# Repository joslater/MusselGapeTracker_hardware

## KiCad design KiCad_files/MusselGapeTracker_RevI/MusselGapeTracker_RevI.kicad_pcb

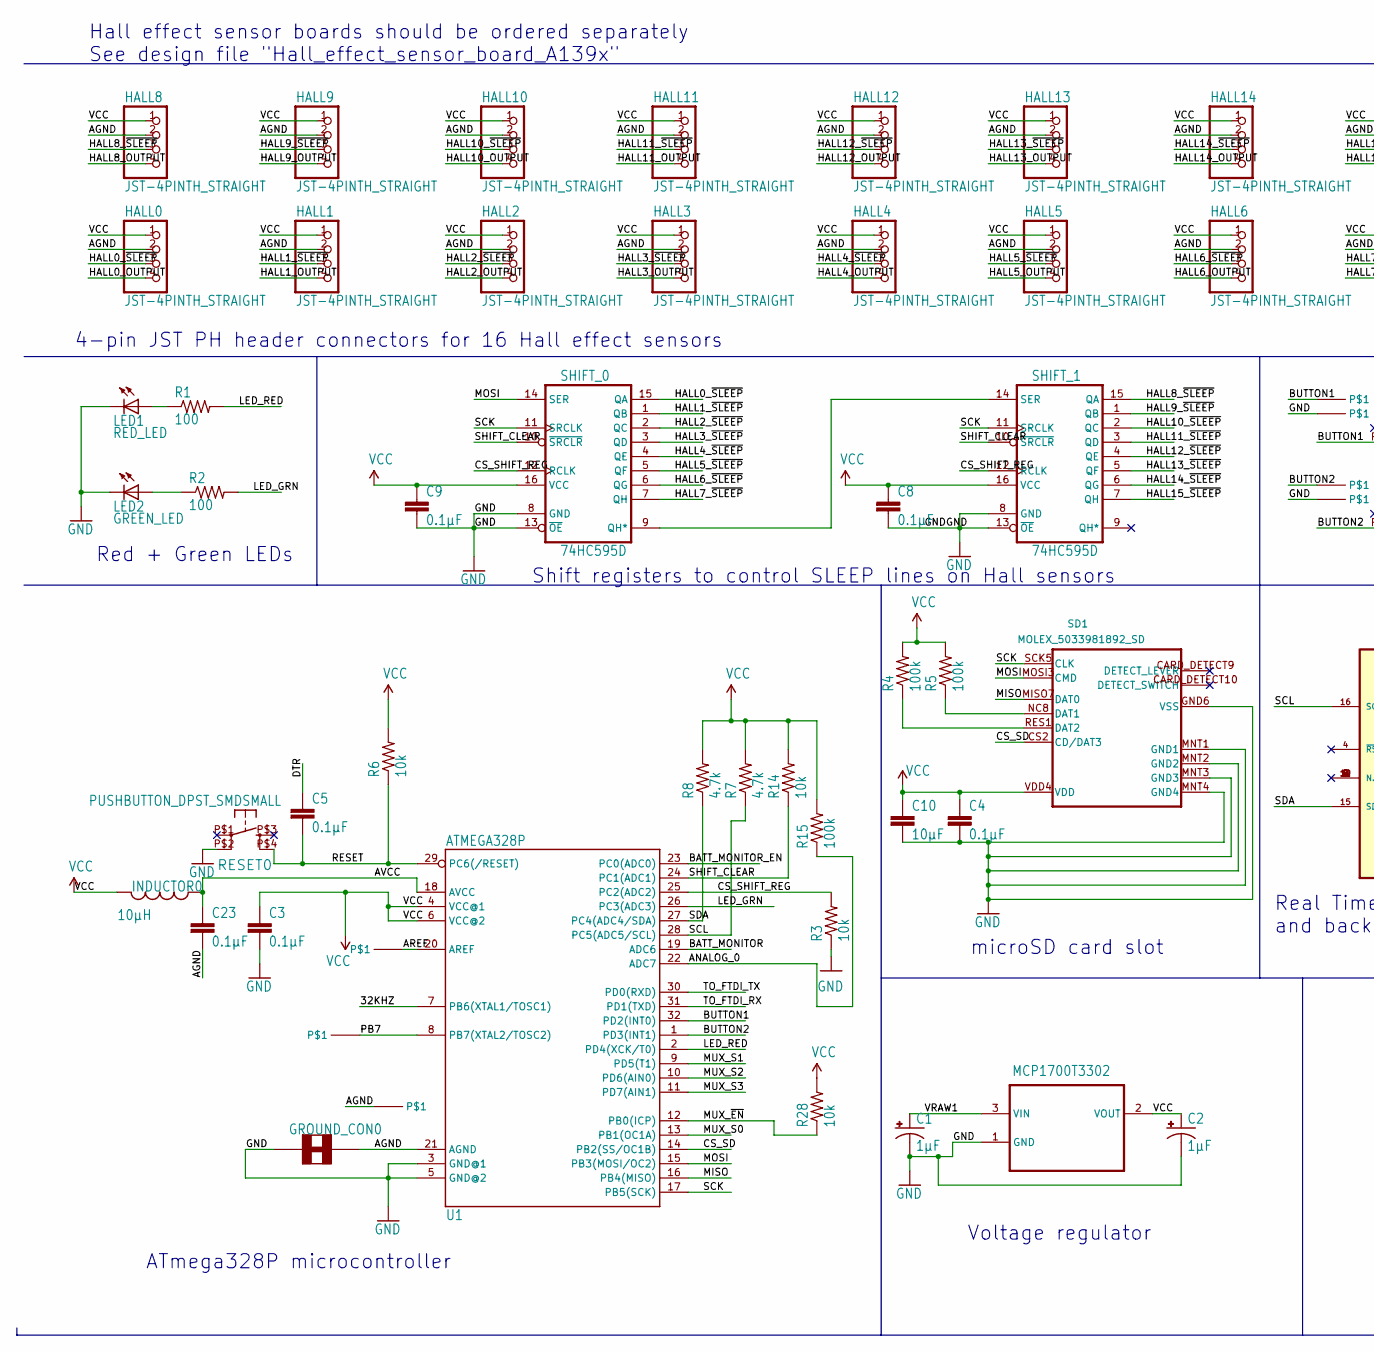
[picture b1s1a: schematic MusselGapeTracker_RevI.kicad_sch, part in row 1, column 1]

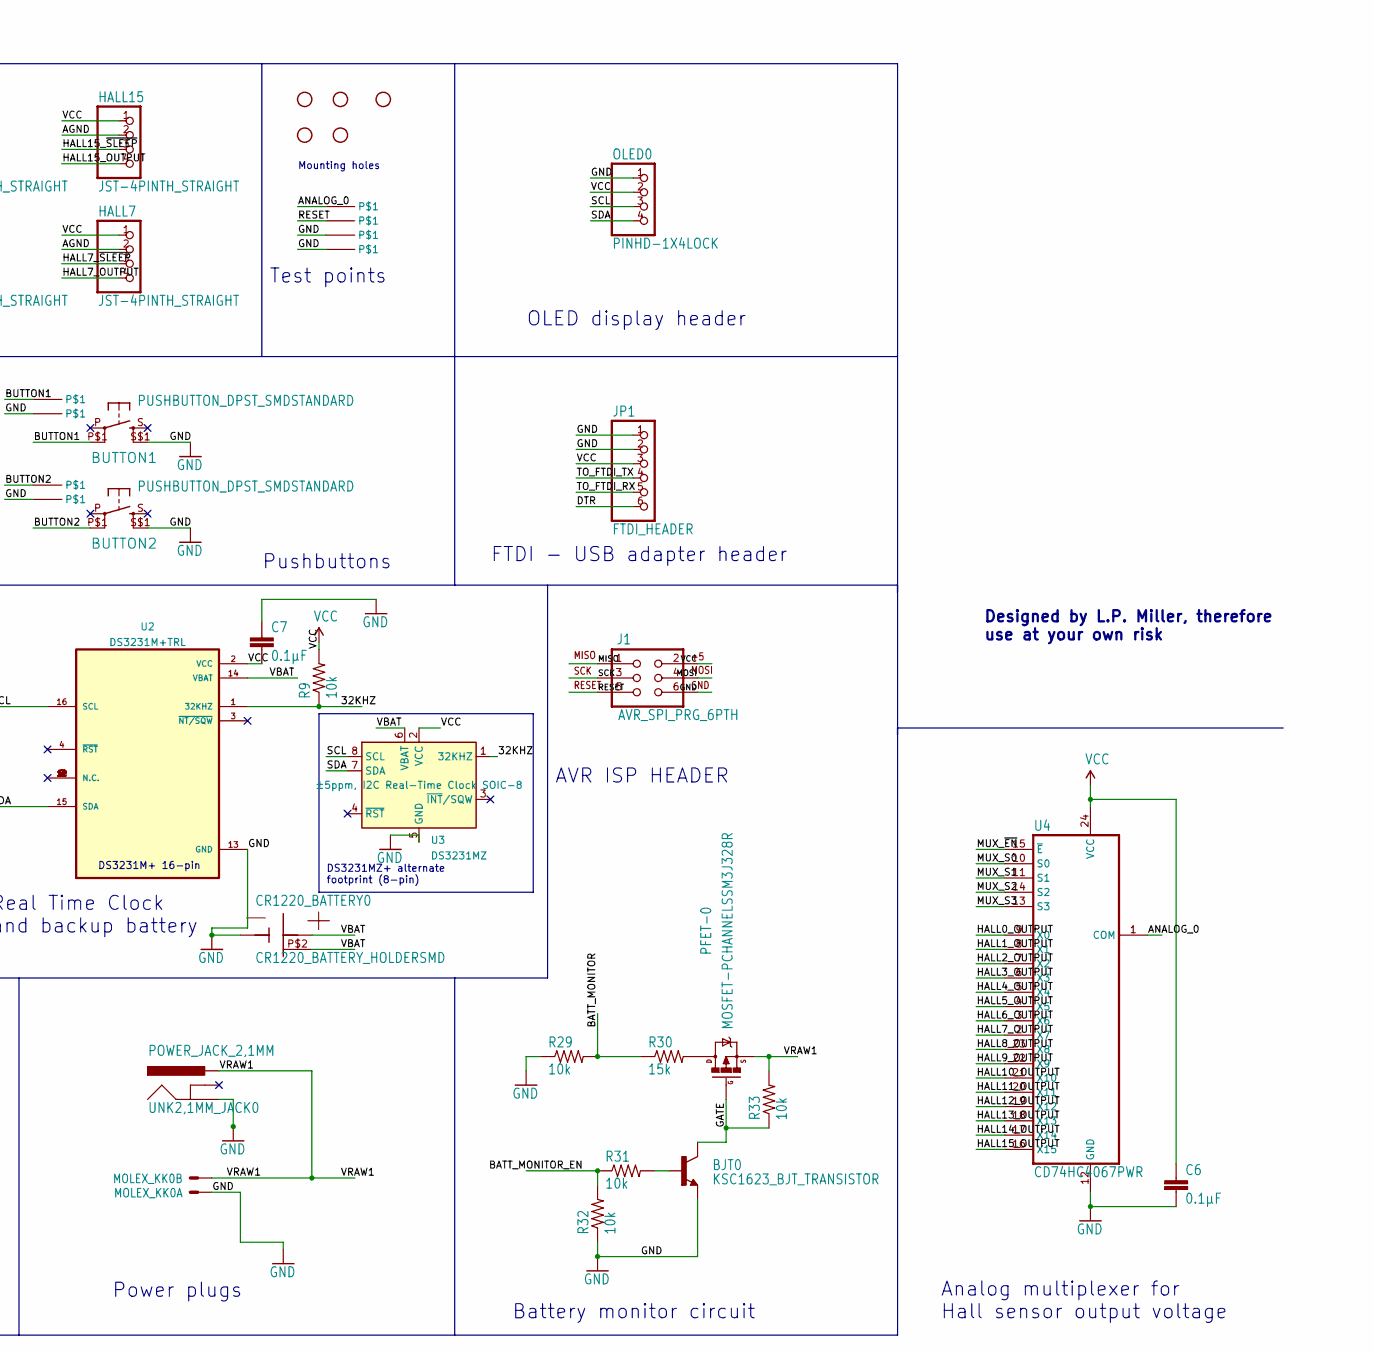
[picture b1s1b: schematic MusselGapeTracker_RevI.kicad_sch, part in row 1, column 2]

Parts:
BJT0: KSC1623_BJT_TRANSISTOR; SOT23
BUTTON1, BUTTON2: PUSHBUTTON_DPST_SMDSTANDARD; PUSHBUTTON_DPST_SMD
C1, C2: 1µF; PANASONIC_B
C3, C4, C5, C6, C7, C8, C9, C23: 0.1µF; R_0603_1608Metric_Pad0.98x0.95mm_HandSolder
C10: 10µF; R_0603_1608Metric_Pad0.98x0.95mm_HandSolder
CR1220_BATTERY0: CR1220_BATTERY_HOLDERSMD; CR1220_BATTERY_HOLDER_SMD
GND0: PINHD-1X1SMALL; 1X01_SMALL
GROUND_CON0: SOLDER_JUMPER_TRACESTANDARD; SJ_2S-TRACE
HALL0, HALL1, HALL2, HALL3, HALL4, HALL5, HALL6, HALL7, HALL8, HALL9, HALL10, HALL11, HALL12, HALL13, HALL14, HALL15: JST-4PINTH_STRAIGHT; JST-PH-4-THM
INDUCTOR0: 10µH; I_0805
J1: AVR_SPI_PRG_6PTH; 2X3
JP1: FTDI_HEADER; 1X06-RIGHT_ANGLE
LED1: RED_LED; CHIPLED_0805
LED2: GREEN_LED; CHIPLED_0805
MCP1700T3302: MCP1700T-3302E/TT; SOT95P237X112-3N
MOLEX_KK0: 22-23-2021
OLED0: PINHD-1X4LOCK; 1X04_LOCK
PB7: PINHD-1X1SMALL; 1X01_SMALL
PFET-0: MOSFET-PCHANNELSSM3J328R; SOT23-3
R1, R2: 100; R_0603_1608Metric_Pad0.98x0.95mm_HandSolder
R3, R6, R9, R14, R28, R29, R31, R32, R33: 10k; R_0603_1608Metric_Pad0.98x0.95mm_HandSolder
R4, R5, R15: 100k; R_0603_1608Metric_Pad0.98x0.95mm_HandSolder
R7, R8: 4.7k; R_0603_1608Metric_Pad0.98x0.95mm_HandSolder
R30: 15k; R_0603_1608Metric_Pad0.98x0.95mm_HandSolder
RESET0: PUSHBUTTON_DPST_SMDSMALL; PUSHBUTTON_SPST_PTS525_SERIES
SD1: MOLEX_5033981892_SD; CONN_503398-1892_MOL; PARTREV A
SHIFT_0, SHIFT_1: 74HC595D; SO16
STANDOFF1, STANDOFF2, STANDOFF3: STAND-OFF4-40; STAND-OFF
STANDOFF4_M2, STANDOFF5_M2: STAND-OFFM2; STAND-OFF_M2
U1: ATMEGA328P; TQFP32-08
U2: DS3231M+TRL; SOIC127P1032X265-16N
U3: DS3231MZ; SOIC-8_3.9x4.9mm_P1.27mm
U4: CD74HC4067PWR; TSSOP-24_4.4x7.8mm_P0.65mm
U$3, U$4, U$6, U$7, U$8, U$9, U$10, U$11, U$17: PINHD-1X1SMALL; 1X01_SMALL
UNK2,1MM_JACK0: POWER_JACK_2,1MM; POWER_JACK_DC_2,1MM

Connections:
/32KHZ: R9.1, U1.7 (PB6(XTAL1/TOSC1)), U2.1 (32KHZ), U3.1 (32KHZ)
/AGND: C23.2, GROUND_CON0.2, HALL0.2, HALL1.2, HALL2.2, HALL3.2, HALL4.2, HALL5.2, HALL6.2, HALL7.2, HALL8.2, HALL9.2, HALL10.2, HALL11.2, HALL12.2, HALL13.2, HALL14.2, HALL15.2, U1.21 (AGND), U$11.1 (P$1_1)
/ANALOG_0: R15.1, U1.22 (ADC7), U4.1 (COM), U$10.1 (P$1_1)
/AREF: U1.20 (AREF), U$17.1 (P$1_1)
/AVCC: C23.1, INDUCTOR0.P$1 (1), U1.18 (AVCC)
/BATT_MONITOR: R29.2, R30.1, U1.19 (ADC6)
/BATT_MONITOR_EN: R31.1, R32.2, U1.23 (PC0(ADC0))
/BUTTON1: BUTTON1.P$1 (P1), U1.32 (PD2(INT0)), U$6.1 (P$1_1)
/BUTTON2: BUTTON2.P$1 (P1), U1.1 (PD3(INT1)), U$8.1 (P$1_1)
/CS_SD: SD1.CS2 (CD/DAT3), U1.14 (PB2(SS/OC1B))
/CS_SHIFT_REG: R3.2, SHIFT_0.12 (RCLK), SHIFT_1.12 (RCLK), U1.25 (PC2(ADC2))
/DTR: C5.1, JP1.6
/GATE: BJT0.3 (C), PFET-0.1 (G), R33.1
/HALL0_OUTPUT: HALL0.4, U4.9 (X0)
/HALL0_~SLEEP: HALL0.3, SHIFT_0.15 (QA)
/HALL1_OUTPUT: HALL1.4, U4.8 (X1)
/HALL1_~SLEEP: HALL1.3, SHIFT_0.1 (QB)
/HALL2_OUTPUT: HALL2.4, U4.7 (X2)
/HALL2_~SLEEP: HALL2.3, SHIFT_0.2 (QC)
/HALL3_OUTPUT: HALL3.4, U4.6 (X3)
/HALL3_~SLEEP: HALL3.3, SHIFT_0.3 (QD)
/HALL4_OUTPUT: HALL4.4, U4.5 (X4)
/HALL4_~SLEEP: HALL4.3, SHIFT_0.4 (QE)
/HALL5_OUTPUT: HALL5.4, U4.4 (X5)
/HALL5_~SLEEP: HALL5.3, SHIFT_0.5 (QF)
/HALL6_OUTPUT: HALL6.4, U4.3 (X6)
/HALL6_~SLEEP: HALL6.3, SHIFT_0.6 (QG)
/HALL7_OUTPUT: HALL7.4, U4.2 (X7)
/HALL7_~SLEEP: HALL7.3, SHIFT_0.7 (QH)
/HALL8_OUTPUT: HALL8.4, U4.23 (X8)
/HALL8_~SLEEP: HALL8.3, SHIFT_1.15 (QA)
/HALL9_OUTPUT: HALL9.4, U4.22 (X9)
/HALL9_~SLEEP: HALL9.3, SHIFT_1.1 (QB)
/HALL10_OUTPUT: HALL10.4, U4.21 (X10)
/HALL10_~SLEEP: HALL10.3, SHIFT_1.2 (QC)
/HALL11_OUTPUT: HALL11.4, U4.20 (X11)
/HALL11_~SLEEP: HALL11.3, SHIFT_1.3 (QD)
/HALL12_OUTPUT: HALL12.4, U4.19 (X12)
/HALL12_~SLEEP: HALL12.3, SHIFT_1.4 (QE)
/HALL13_OUTPUT: HALL13.4, U4.18 (X13)
/HALL13_~SLEEP: HALL13.3, SHIFT_1.5 (QF)
/HALL14_OUTPUT: HALL14.4, U4.17 (X14)
/HALL14_~SLEEP: HALL14.3, SHIFT_1.6 (QG)
/HALL15_OUTPUT: HALL15.4, U4.16 (X15)
/HALL15_~SLEEP: HALL15.3, SHIFT_1.7 (QH)
/LED_GRN: R2.2, U1.26 (PC3(ADC3))
/LED_RED: R1.2, U1.2 (PD4(XCK/T0))
/MISO: J1.1, SD1.MISO7 (DAT0), U1.16 (PB4(MISO))
/MOSI: J1.4, SD1.MOSI3 (CMD), SHIFT_0.14 (SER), U1.15 (PB3(MOSI/OC2))
/MUX_S0: U1.13 (PB1(OC1A)), U4.10 (S0)
/MUX_S1: U1.9 (PD5(T1)), U4.11 (S1)
/MUX_S2: U1.10 (PD6(AIN0)), U4.14 (S2)
/MUX_S3: U1.11 (PD7(AIN1)), U4.13 (S3)
/MUX_~EN: R28.1, U1.12 (PB0(ICP)), U4.15 (~E)
/PB7: PB7.1 (P$1_1), U1.8 (PB7(XTAL2/TOSC2))
/RESET: C5.2, J1.5, R6.1, RESET0.P$4 (S1), U1.29 (PC6(/RESET)), U$3.1 (P$1_1)
/SCK: J1.3, SD1.SCK5 (CLK), SHIFT_0.11 (SRCLK), SHIFT_1.11 (SRCLK), U1.17 (PB5(SCK))
/SCL: OLED0.3, R7.1, U1.28 (PC5(ADC5/SCL)), U2.16 (SCL), U3.8 (SCL)
/SDA: OLED0.4, R8.1, U1.27 (PC4(ADC4/SDA)), U2.15 (SDA), U3.7 (SDA)
/SHIFT_CLEAR: R14.1, SHIFT_0.10 (~SRCLR), SHIFT_1.10 (~SRCLR), U1.24 (PC1(ADC1))
/TO_FTDI_RX: JP1.5, U1.31 (PD1(TXD))
/TO_FTDI_TX: JP1.4, U1.30 (PD0(RXD))
/VBAT: CR1220_BATTERY0.P$1 (VBAT), CR1220_BATTERY0.P$2, U2.14 (VBAT), U3.6 (VBAT)
/VRAW1: C1.+, MCP1700T3302.3 (VIN), MOLEX_KK0.2 (S), PFET-0.2 (S), R33.2, UNK2,1MM_JACK0.P$1 (PWR)
GND: BJT0.2 (E), BUTTON1.S$1 (S1), BUTTON2.S$1 (S1), C1.-, C2.-, C3.2, C4.2, C6.2, C7.1, C8.2, C9.2, C10.2, CR1220_BATTERY0.GND, GND0.1 (P$1_1), GROUND_CON0.1, J1.6, JP1.1, JP1.2, LED1.C, LED2.C, MCP1700T3302.1 (GND), MOLEX_KK0.1 (S), OLED0.1, R3.1, R29.1, R32.1, RESET0.P$2 (P1), SD1.GND6 (VSS), SD1.MNT1 (GND1), SD1.MNT2 (GND2), SD1.MNT3 (GND3), SD1.MNT4 (GND4), SHIFT_0.8 (GND), SHIFT_0.13 (~OE), SHIFT_1.8 (GND), SHIFT_1.13 (~OE), U1.3 (GND@1), U1.5 (GND@2), U2.13 (GND), U3.5 (GND), U4.12 (GND), U$4.1 (P$1_1), U$7.1 (P$1_1), U$9.1 (P$1_1), UNK2,1MM_JACK0.P$2 (GND)
unnamed: BJT0.1 (B), R31.2
unnamed: LED1.A, R1.1
unnamed: LED2.A, R2.1
unnamed: PFET-0.3 (D), R30.2
unnamed: R5.1, SD1.NC8 (DAT1)
unnamed: R4.1, SD1.RES1 (DAT2)
unnamed: SHIFT_0.9 (QH*), SHIFT_1.14 (SER)
VCC: C2.+, C3.1, C4.1, C6.1, C7.2, C8.1, C9.1, C10.1, HALL0.1, HALL1.1, HALL2.1, HALL3.1, HALL4.1, HALL5.1, HALL6.1, HALL7.1, HALL8.1, HALL9.1, HALL10.1, HALL11.1, HALL12.1, HALL13.1, HALL14.1, HALL15.1, INDUCTOR0.P$2 (2), J1.2, JP1.3, MCP1700T3302.2 (VOUT), OLED0.2, R4.2, R5.2, R6.2, R7.2, R8.2, R9.2, R14.2, R15.2, R28.2, SD1.VDD4 (VDD), SHIFT_0.16 (VCC), SHIFT_1.16 (VCC), U1.4 (VCC@1), U1.6 (VCC@2), U2.2 (VCC), U3.2 (VCC), U4.24 (VCC)

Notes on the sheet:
Voltage regulator
OLED display header
DS3231M+ 16-pin
microSD card slot
Real Time Clock and backup battery
Battery monitor circuit
4-pin JST PH header connectors for 16 Hall effect sensors
Hall effect sensor boards should be ordered separately See design file "Hall_effect_sensor_board_A139x"
Pushbuttons
Test points
Designed by L.P. Miller, therefore use at your own risk
ATmega328P microcontroller
FTDI - USB adapter header
Analog multiplexer for Hall sensor output voltage
Power plugs
Mounting holes
Shift registers to control SLEEP lines on Hall sensors
DS3231MZ+ alternate footprint (8-pin)
AVR ISP HEADER
Red + Green LEDs

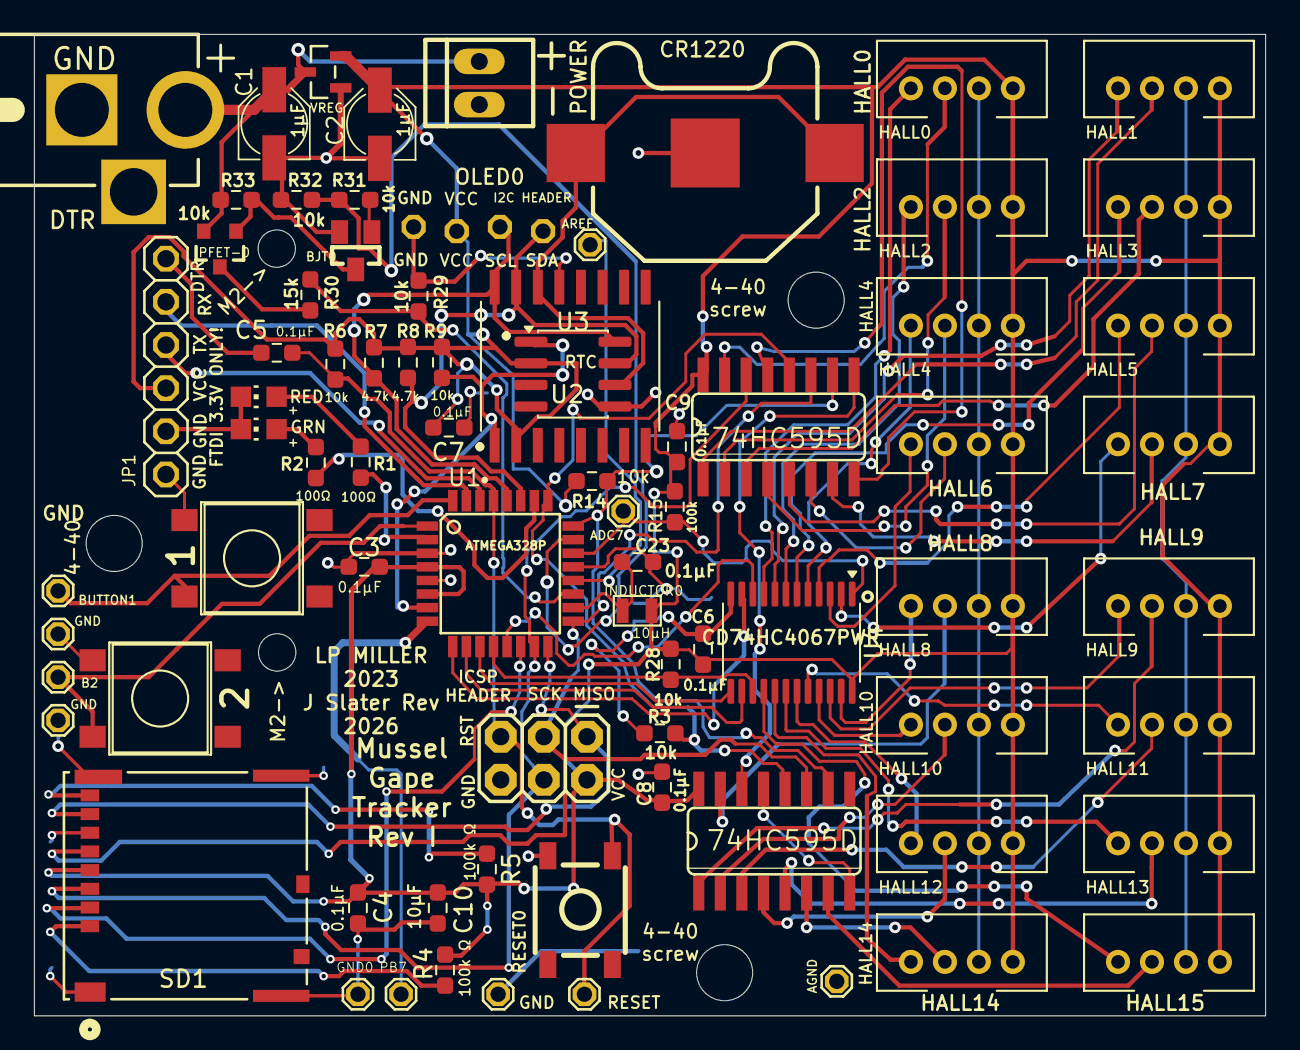
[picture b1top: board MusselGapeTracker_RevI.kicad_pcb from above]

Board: 2 copper layers, 72.5 x 57.8 mm, 83 parts (1 on the bottom side), 73 nets.

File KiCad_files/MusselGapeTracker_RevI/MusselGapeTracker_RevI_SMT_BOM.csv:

Item,Qty,Reference,Description,KiCad Value,Supplier,Supplier P/N
1,1,BJT0,BJT NPN Transistor 50V 2A SOT23-3 package,KSC1623_BJT_TRANSISTOR,DigiKey,FMMT619CT-ND
2,2,"BUTTON1,BUTTON2","Pushbutton switch SPST tactile, SMD",PUSHBUTTON_DPST_SMDSTANDARD,DigiKey,SW836CT-ND
3,2,"C1,C2","Capacitor, surface mount 1uF 35V, electrolytic, Panasonic FC series, size code B",1µF,DigiKey,PCE4024CT-ND
4,8,"C3,C4,C5,C6,C7,C8,C9,C23","Capacitor, 0603 0.1µF 16V ceramic",0.1µF,DigiKey,399-1096-1-ND
5,1,C10,"Capacitor, 0603 10µF X5R",10µF,DigiKey,311-3486-2-ND
6,1,CR1220_BATTERY0,CR1220 Battery holder,CR1220_BATTERY_HOLDERSMD,DigiKey,36-3000-ND
7,1,INDUCTOR0,"Inductor, 10µH 150mA, 360 mOhm",10µH,DigiKey,587-2045-1-ND
8,1,LED1,"LED, Red 0805",RED_LED,DigiKey,160-1427-1-ND
9,1,LED2,"LED, Green 0805",GREEN_LED,DigiKey,160-1423-1-ND
10,1,MCP1700T-3302,Voltage regulator MCP-1700T-3002 3.0V (or 3.3V version),MCP1700T-3302E{slash}TT,DigiKey,MCP1700T-3002E/TTCT-ND
11,1,PFET-0,P-Channel 20 V 6A (Ta) 1W (Ta) Surface Mount SOT-23F,MOSFET-PCHANNELSSM3J328R,DigiKey,SSM3J328RLFCT-ND
12,2,"R1,R2","Resistor, 0603 100ohm",100,DigiKey,311-100GRCT-ND
13,9,"R3,R6,R9,R14,R28,R29,R31,R32,R33","Resistor, 0603 10 k ohm",10k,DigiKey,311-10KGRCT-ND
14,3,"R4,R5,R15","Resistor, 0603 100 k ohmÊ",100k,DigiKey,311-100KGRCT-ND
15,2,"R7,R8","Resistor, 0603 4.7k ohm",4.7k,DigiKey,311-4.7KGRCT-ND
16,1,R30,"Resistor, 0603 15 k ohmÊ",15k,DigiKey,311-15KGRCT-ND
17,1,RESET0,"pushbutton surface mount (small, 1.5mm height)",PUSHBUTTON_DPST_SMDSMALL,DigiKey,CKN9104CT-ND
18,1,SD1,MicroSD card slot 5033981892,MOLEX_5033981892_SD,DigiKey,WM11190CT-ND
19,2,"SHIFT_0,SHIFT_1",Shift register 74HC595D,74HC595D,DigiKey,296-31822-1-ND
20,1,U1,ATmega328P 32-TQFP,ATMEGA328P,DigiKey,ATMEGA328P-AURCT-ND
21,1,U3,"Real Time Clock, DS3231SN#Ê SO-16 footprint",DS3231MZ,DigiKey,DS3231SN#-ND
22,1,U4,"CD74HC4067PWR multiplexer 16 channel (24-TSSOP 4.4x7.8mm, 0.65mm pitch)",CD74HC4067PWR,DigiKey,296-CD74HC4067PWRCT-ND

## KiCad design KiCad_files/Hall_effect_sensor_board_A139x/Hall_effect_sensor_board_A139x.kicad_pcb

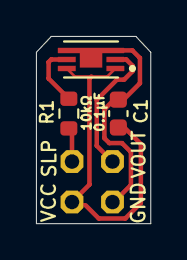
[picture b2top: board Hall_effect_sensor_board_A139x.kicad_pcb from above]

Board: 2 copper layers, 6.4 x 10.4 mm, 4 parts (0 on the bottom side), 5 nets.

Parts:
C1: 0.1µF; C_0603_1608Metric
HALL1_HEADER1: PINHD-2X21.5MM_SILK; 2X2_2.25MM
R1: 10kΩ; R_0603_1608Metric
U1: A1395SEHLT-T; SENSOR_A1395SEHLT-T

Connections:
/HALL1_GND: C1.2, HALL1_HEADER1.P$1 (1), U1.3 (GND), U1.4 (GND)
/HALL1_VCC: C1.1, HALL1_HEADER1.P$2 (2), U1.1 (VCC), U1.6 (VREF)
/HALL1_VOUT: HALL1_HEADER1.P$3 (3), U1.2 (OUT)
/HALL1_~SLEEP_IN: HALL1_HEADER1.P$4 (4), R1.1
/~SLEEP1: R1.2, U1.5 (~SLEEP)

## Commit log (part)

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2026-04-09 replace Molex 502774-0891 with GCT MEM2052-00-195-00-A
2026-04-10 replace Molex 502774-0891 with GCT MEM2052-00-195-00-A
    Pre-existing DRC errors (34) unrelated to this change.
2026-04-10 add gitignore for DS_store files
2026-04-10 add gitignore and remove DS_Store files
2026-04-10 remove all DS_Store files
2026-04-10 Update p-channel mosfet from BSH203 to SSM3J328R
2026-04-21 Moved changes to Rev I and fixed DRC errors
    Made new copy of KiCad project in Rev I and fixed some electric rules checker errors and warnings and some design rules checker errors and warnings
2026-04-21 Copied over and updated parts list to Rev I
2026-04-21 Updated parts list with cable sub
2026-05-08 Edits to pcb and parts list
2026-05-08 parts list edit
2026-05-08 Updated KiCad and Parts list for new SD Card Slot
    Updated KiCad schematic, PCB, and parts list for new SD card slot Molex 5033981892
2026-05-10 Fix PCB DRC errors and updated parts list
    Updated parts list for more accurate DS3231 chip
2026-05-10 Created purchase list
2026-05-10 Generate gerber files
2026-05-10 Update purchase list
2026-06-03 Fixed SD card mount traces
    Ran SD card traces on bottom instead of top to avoid sd mount prohibition area
2026-06-09 Generated new gerbers
    Generated new gerber files after modifying SD card traces
